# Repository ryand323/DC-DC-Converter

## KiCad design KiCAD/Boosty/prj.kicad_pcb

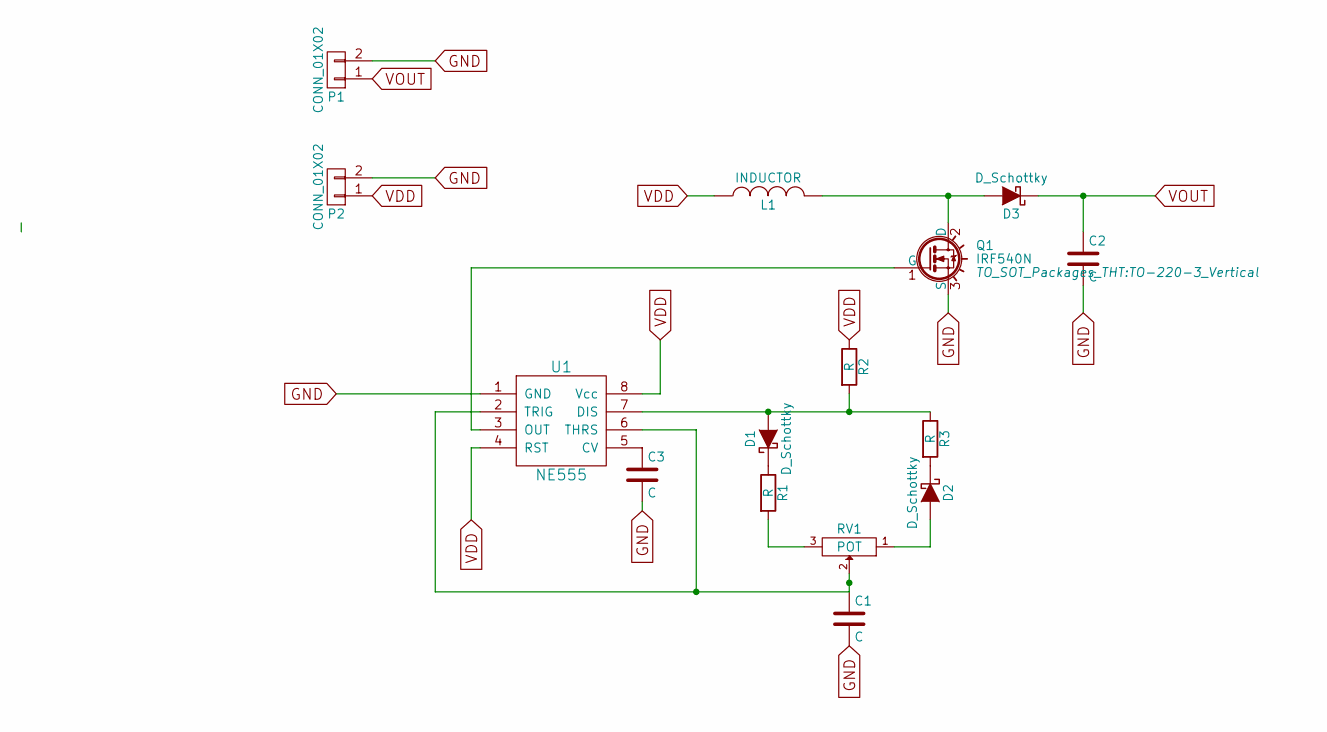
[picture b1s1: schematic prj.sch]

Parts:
C1, C3: C; C_Disc_D9.0mm_W5.0mm_P7.50mm
C2: C; CP_Radial_D10.0mm_P5.00mm
D1, D2, D3: D_Schottky; D_DO-41_SOD81_P7.62mm_Horizontal
L1: INDUCTOR; CP_Radial_D10.0mm_P5.00mm
P1, P2: CONN_01X02; Pin_Header_Angled_1x02_Pitch2.54mm
Q1: IRF540N; TO-220-3_Vertical
R1, R2, R3: R; R_Axial_DIN0207_L6.3mm_D2.5mm_P10.16mm_Horizontal
RV1: POT; Potentiometer_Trimmer_Bourns_3299W
U1: NE555; DIP-8_W7.62mm_Socket

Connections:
GND: C1.2, C2.2, C3.2, P1.2, P2.2, Q1.3 (S), U1.1 (GND)
unnamed: C1.1, RV1.2, U1.2 (TRIG), U1.6 (THRS)
unnamed: C3.1, U1.5 (CV)
unnamed: D1.1 (K), R1.1
unnamed: D1.2 (A), R2.2, R3.1, U1.7 (DIS)
unnamed: D2.1 (K), R3.2
unnamed: D2.2 (A), RV1.1
unnamed: D3.2 (A), L1.2, Q1.2 (D)
unnamed: Q1.1 (G), U1.3 (OUT)
unnamed: R1.2, RV1.3
VDD: L1.1, P2.1, R2.1, U1.4 (RST), U1.8 (Vcc)
VOUT: C2.1, D3.1 (K), P1.1

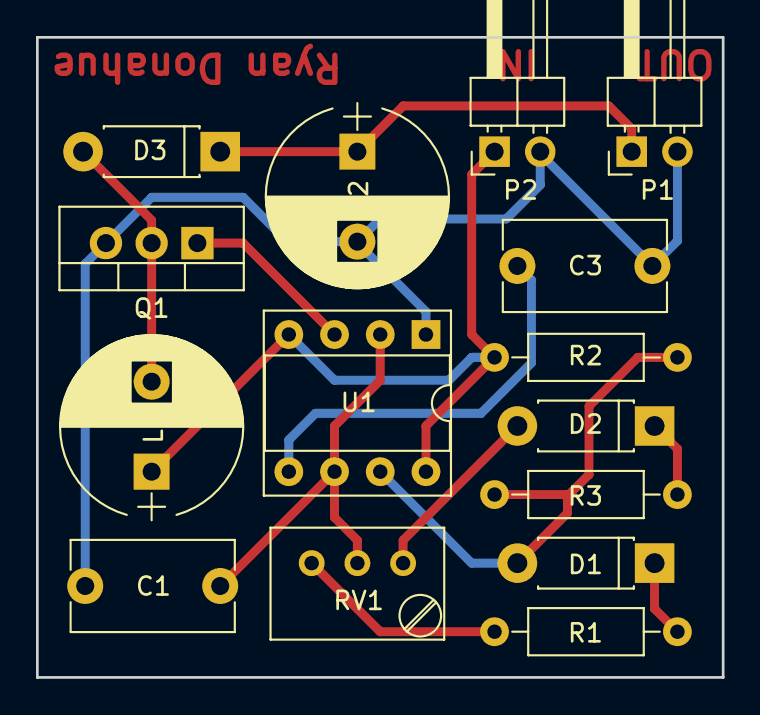
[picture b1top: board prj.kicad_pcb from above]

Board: 2 copper layers, 38.1 x 35.6 mm, 15 parts (0 on the bottom side), 12 nets.

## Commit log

2018-12-04 project
